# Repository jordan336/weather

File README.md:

## Weather Station 
### Jordan Ebel

STM32F0 ARM Cortex M0 based weather station with temperature, UV, light, 
and soil moisture monitoring.  The board is powered with 5V from the USB 
connector.  The board includes a standard RJ-45 Ethernet jack with built-in
magnetics.  I2C, SWD, and some GPIO pins are broken out to connectors for
debug and test.

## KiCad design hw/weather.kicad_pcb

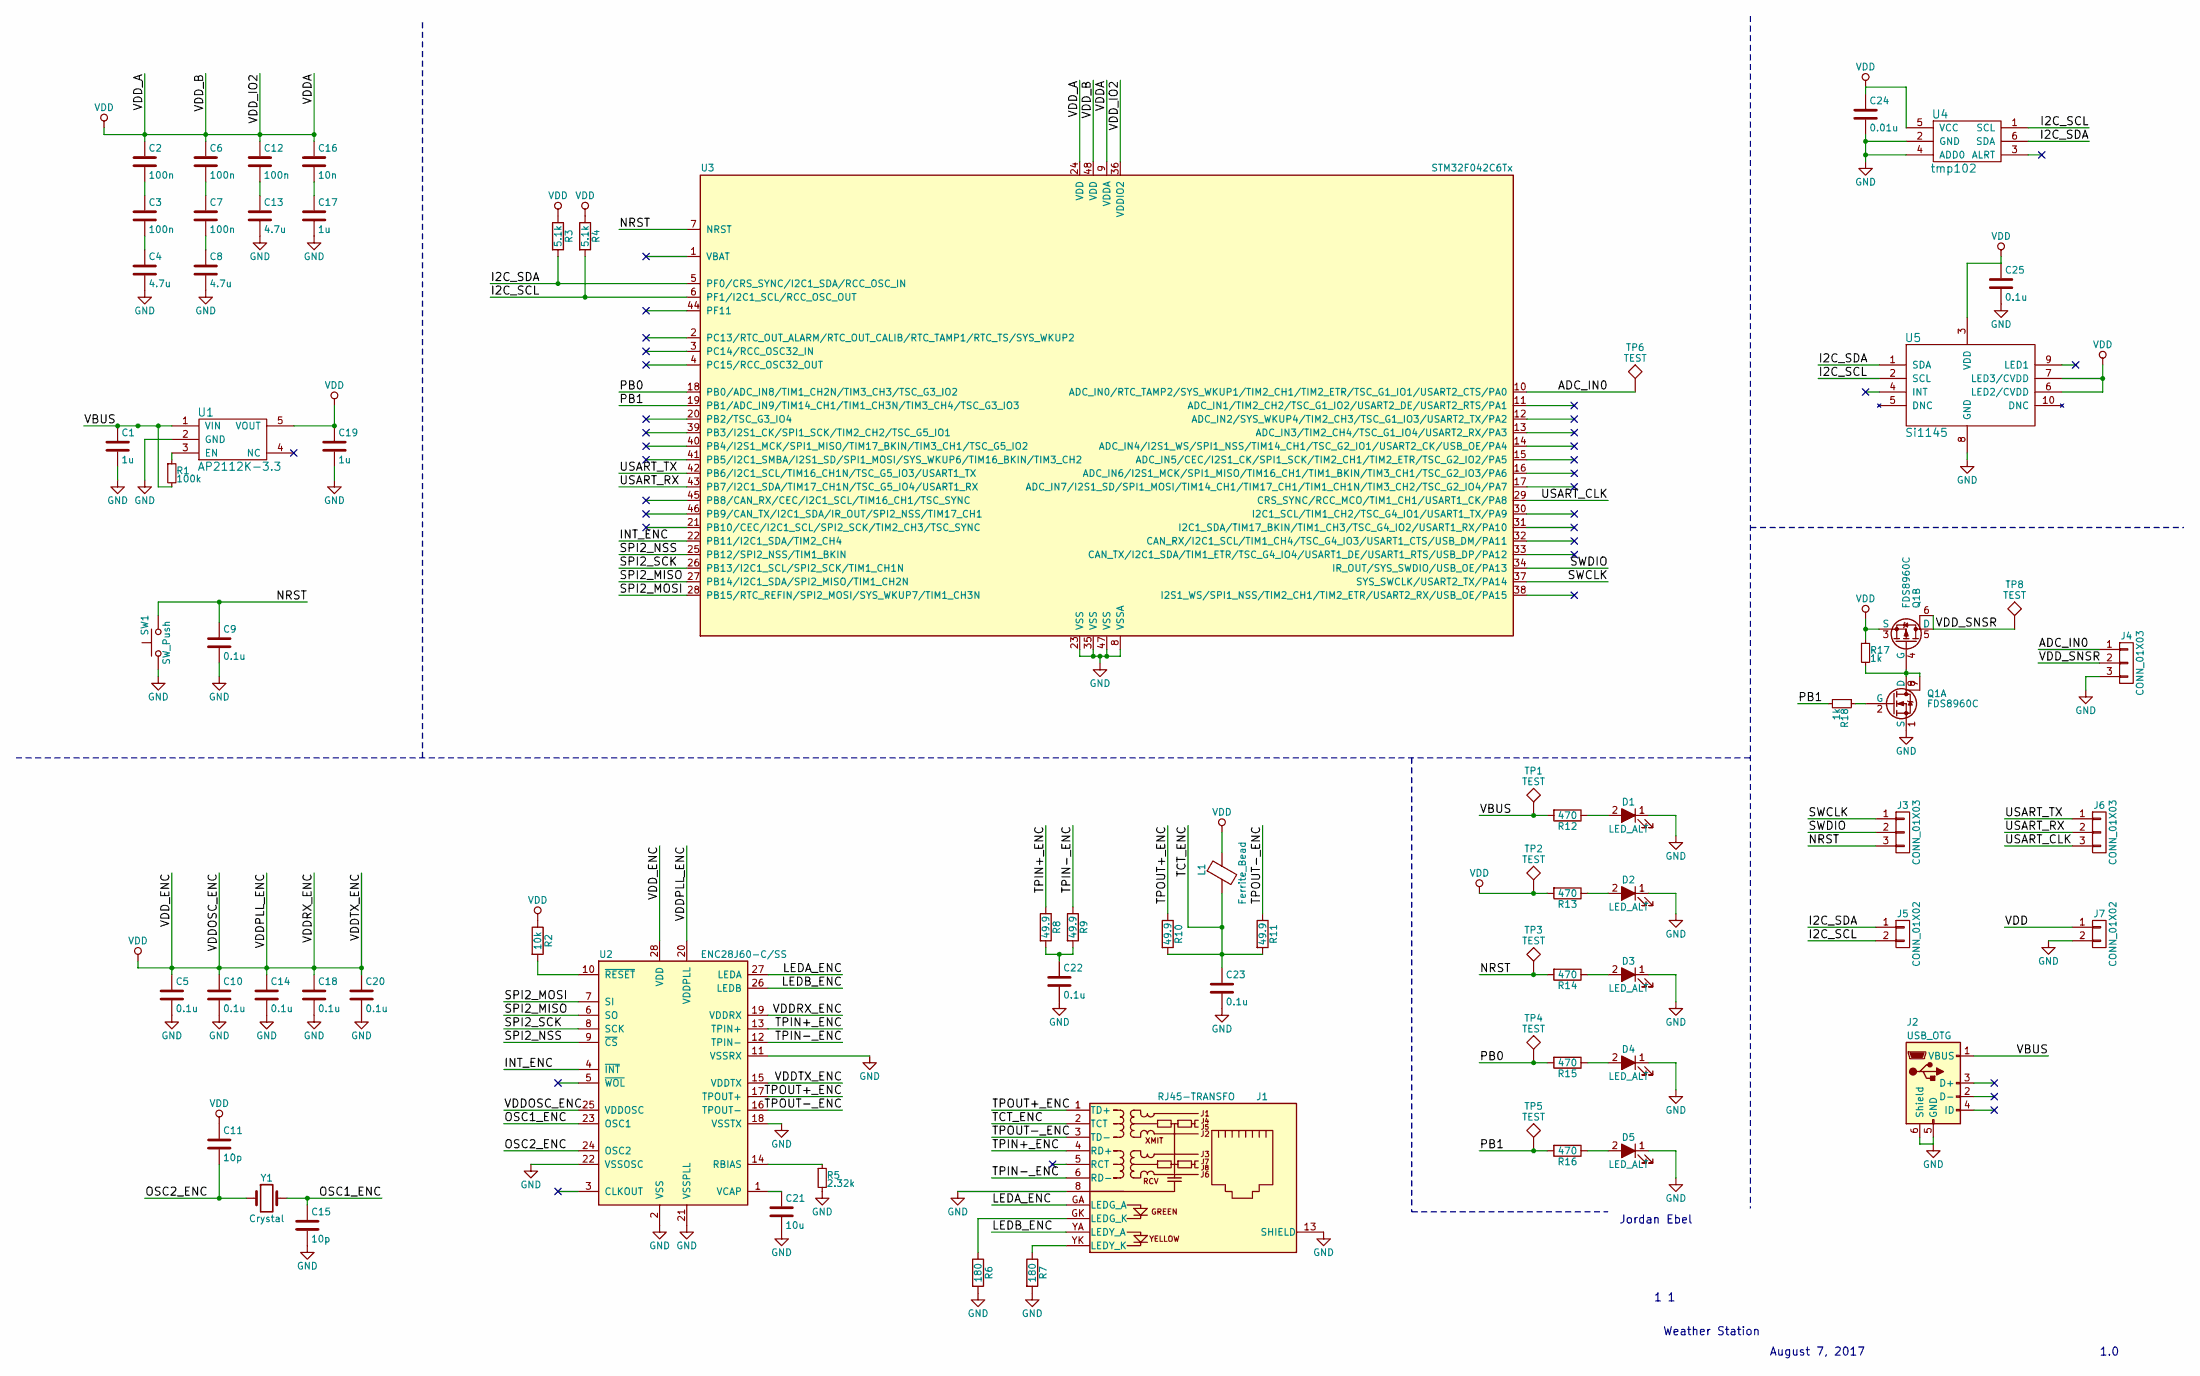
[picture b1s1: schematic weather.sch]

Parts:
C1, C17, C19: 1u; C_1206_HandSoldering
C2, C3, C6, C7, C12: 100n; C_1206_HandSoldering
C4, C8, C13: 4.7u; C_1206_HandSoldering
C5, C9, C10, C14, C18, C20, C22, C23, C25: 0.1u; C_1206_HandSoldering
C11, C15: 10p; C_1206_HandSoldering
C16: 10n; C_1206_HandSoldering
C21: 10u; C_1206_HandSoldering
C24: 0.01u; C_1206_HandSoldering
D1, D2, D3, D4, D5: LED_ALT; LED_1206_HandSoldering
J1: RJ45-TRANSFO; RJ45_TRANSFO
J2: USB_OTG; USB_Micro-B
J3, J4, J6: CONN_01X03; Pin_Header_Straight_1x03_Pitch2.54mm
J5, J7: CONN_01X02; Pin_Header_Straight_1x02_Pitch2.54mm
L1: Ferrite_Bead; L_Vishay_IHSM-3825
Q1: FDS8960C; SOIC-8_3.9x4.9mm_Pitch1.27mm
R1: 100k; R_1206_HandSoldering
R2: 10k; R_1206_HandSoldering
R3, R4: 5.1k; R_1206_HandSoldering
R5: 2.32k; R_1206_HandSoldering
R6, R7: 180; R_1206_HandSoldering
R8, R9, R10, R11: 49.9; R_1206_HandSoldering
R12, R13, R14, R15, R16: 470; R_1206_HandSoldering
R17, R18: 1k; R_1206_HandSoldering
SW1: SW_Push; SW_TH_Tactile_Omron_B3F-10xx
TP1, TP2, TP3, TP4, TP5, TP6, TP8: TEST; Measurement_Point_Round-TH_Big
U1: AP2112K-3.3; SOT-23-5_HandSoldering
U2: ENC28J60-C/SS; SSOP-28_5.3x10.2mm_Pitch0.65mm
U3: STM32F042C6Tx; LQFP-48_7x7mm_Pitch0.5mm
U4: tmp102; SOT-563
U5: Si1145; 10-QFN
Y1: Crystal; Crystal_SMD_HC49-SD_HandSoldering

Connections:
/ADC_IN0: J4.1, TP6.1, U3.10 (ADC_IN0/RTC_TAMP2/SYS_WKUP1/TIM2_CH1/TI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)
/I2C_SCL: J5.2, R4.2, U3.6 (PF1/I2C1_SCL/RCC_OSC_OUT), U4.1 (SCL), U5.2 (SCL)
/I2C_SDA: J5.1, R3.2, U3.5 (PF0/CRS_SYNC/I2C1_SDA/RCC_OSC_IN), U4.6 (SDA), U5.1 (SDA)
/INT_ENC: U2.4 (~INT), U3.22 (PB11/I2C1_SDA/TIM2_CH4)
/LEDA_ENC: J1.GA (LEDG_A), U2.27 (LEDA)
/LEDB_ENC: J1.YA (LEDY_A), U2.26 (LEDB)
/NRST: C9.1, J3.3, R14.2, SW1.2, TP3.1, U3.7 (NRST)
/OSC1_ENC: C15.1, U2.23 (OSC1), Y1.2
/OSC2_ENC: C11.2, U2.24 (OSC2), Y1.1
/PB0: R15.2, TP4.1, U3.18 (PB0/ADC_IN8/TIM1_CH2N/TIM3_CH3/TSC_G3_I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)
/PB1: R16.2, R18.2, TP5.1, U3.19 (PB1/ADC_IN9/TIM14_CH1/TIM1_CH3N/TIM3_CH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)
/SPI2_MISO: U2.6 (SO), U3.27 (PB14/I2C1_SDA/SPI2_MISO/TIM1_CH2N)
/SPI2_MOSI: U2.7 (SI), U3.28 (PB15/RTC_REFIN/SPI2_MOSI/SYS_WKUP7/TIM1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)
/SPI2_NSS: U2.9 (~CS), U3.25 (PB12/SPI2_NSS/TIM1_BKIN)
/SPI2_SCK: U2.8 (SCK), U3.26 (PB13/I2C1_SCL/SPI2_SCK/TIM1_CH1N)
/SWCLK: J3.1, U3.37 (SYS_SWCLK/USART2_TX/PA14)
/SWDIO: J3.2, U3.34 (IR_OUT/SYS_SWDIO/USB_OE/PA13)
/TCT_ENC: C23.1, J1.2 (TCT), L1.2, R10.2, R11.2
/TPIN+_ENC: J1.4 (RD+), R8.1, U2.13 (TPIN+)
/TPIN-_ENC: J1.6 (RD-), R9.1, U2.12 (TPIN-)
/TPOUT+_ENC: J1.1 (TD+), R10.1, U2.17 (TPOUT+)
/TPOUT-_ENC: J1.3 (TD-), R11.1, U2.16 (TPOUT-)
/USART_CLK: J6.3, U3.29 (CRS_SYNC/RCC_MCO/TIM1_CH1/USART1_CK/PA8)
/USART_RX: J6.2, U3.43 (PB7/I2C1_SDA/TIM17_CH1N/TSC_G5_IO4/USAR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)
/USART_TX: J6.1, U3.42 (PB6/I2C1_SCL/TIM16_CH1N/TSC_G5_IO3/USAR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)
/VBUS: C1.1, J2.1 (VBUS), R1.2, R12.2, TP1.1, U1.1 (VIN)
/VDD_SNSR: J4.2, Q1.5 (D), Q1.6, TP8.1
GND: C1.2, C4.2, C5.2, C8.2, C9.2, C10.2, C13.2, C14.2, C15.2, C17.2, C18.2, C19.2, C20.2, C21.2, C22.2, C23.2, C24.2, C25.2, D1.1 (K), D2.1 (K), D3.1 (K), D4.1 (K), D5.1 (K), J1.8, J1.13 (SHIELD), J2.5 (GND), J2.6 (Shield), J4.3, J7.2, Q1.1 (S), R5.2, R6.2, R7.2, SW1.1, U1.2 (GND), U2.2 (VSS), U2.11 (VSSRX), U2.18 (VSSTX), U2.21 (VSSPLL), U2.22 (VSSOSC), U3.8 (VSSA), U3.23 (VSS), U3.35 (VSS), U3.47 (VSS), U4.2 (GND), U4.4 (ADD0), U5.8 (GND)
unnamed: C2.2, C3.1
unnamed: C3.2, C4.1
unnamed: C6.2, C7.1
unnamed: C7.2, C8.1
unnamed: C12.2, C13.1
unnamed: C16.2, C17.1
unnamed: C21.1, U2.1 (VCAP)
unnamed: C22.1, R8.2, R9.2
unnamed: D1.2 (A), R12.1
unnamed: D2.2 (A), R13.1
unnamed: D3.2 (A), R14.1
unnamed: D4.2 (A), R15.1
unnamed: D5.2 (A), R16.1
unnamed: J1.GK (LEDG_K), R6.1
unnamed: J1.YK (LEDY_K), R7.1
unnamed: Q1.2 (G), R18.1
unnamed: Q1.4 (G), Q1.7, Q1.8 (D), R17.2
unnamed: R1.1, U1.3 (EN)
unnamed: R2.2, U2.10 (~RESET)
unnamed: R5.1, U2.14 (RBIAS)
VDD: C2.1, C5.1, C6.1, C10.1, C11.1, C12.1, C14.1, C16.1, C18.1, C19.1, C20.1, C24.1, C25.1, J7.1, L1.1, Q1.3 (S), R2.1, R3.1, R4.1, R13.2, R17.1, TP2.1, U1.5 (VOUT), U2.15 (VDDTX), U2.19 (VDDRX), U2.20 (VDDPLL), U2.25 (VDDOSC), U2.28 (VDD), U3.9 (VDDA), U3.24 (VDD), U3.36 (VDDIO2), U3.48 (VDD), U4.5 (VCC), U5.3 (VDD), U5.6 (LED2/CVDD), U5.7 (LED3/CVDD)

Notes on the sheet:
1.0
August 7, 2017
Weather Station
Jordan Ebel

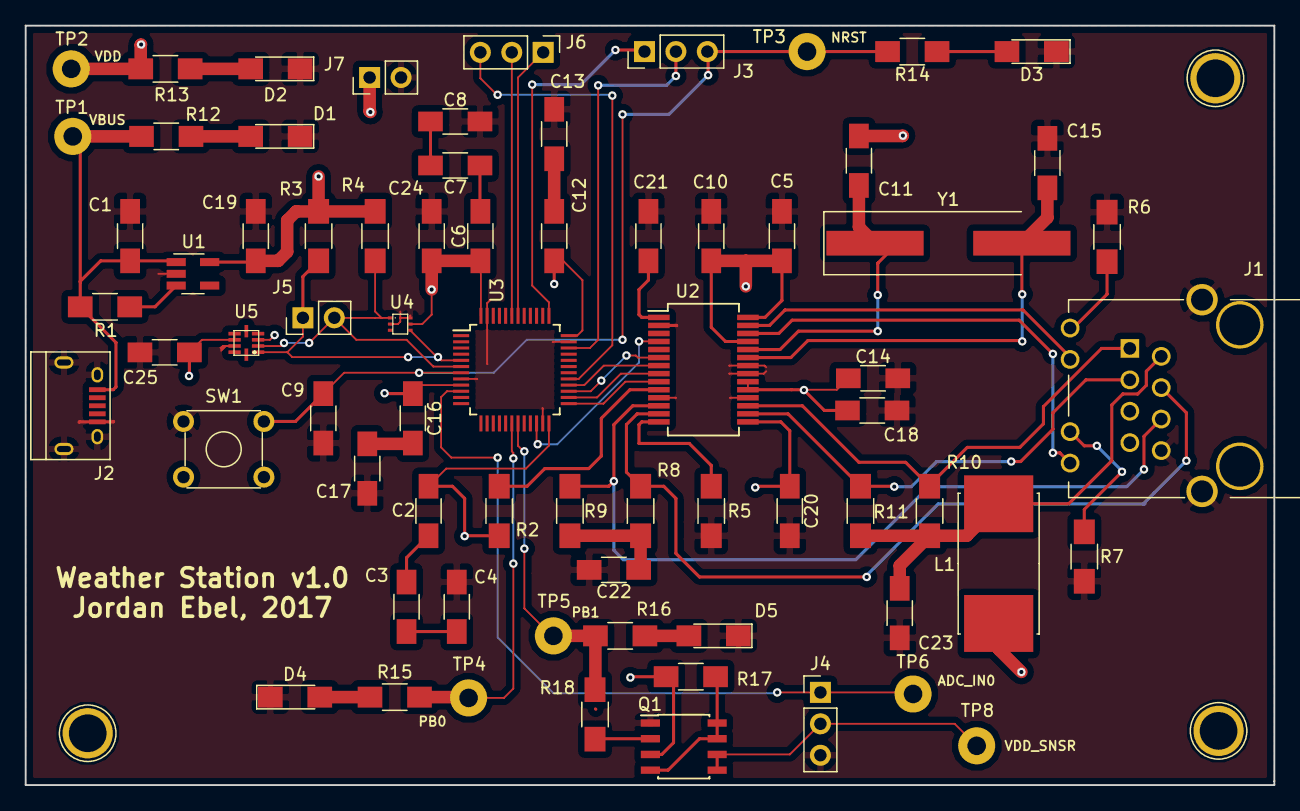
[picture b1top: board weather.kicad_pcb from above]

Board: 2 copper layers, 101.0 x 61.4 mm, 71 parts (0 on the bottom side), 49 nets.

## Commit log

2017-08-14 Adding README.md
2017-08-14 Adding docs.
2017-08-14 Adding hw dir.
2017-08-14 Adding license
2017-08-15 Removing temporary files
2017-08-15 Adding gitignore
2017-08-21 Updating README
